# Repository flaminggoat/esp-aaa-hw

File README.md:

# ESP AAA

An AAA battery powered ESP32-C3 board.

# Revisions

* v1.0 - Faulty, Will not start up from an AAA cell, unsuitable boost converter IC used, which requires 1.8V to startup.

# License

Licensed under CERN-OHL-W 
https://cern-ohl.web.cern.ch/

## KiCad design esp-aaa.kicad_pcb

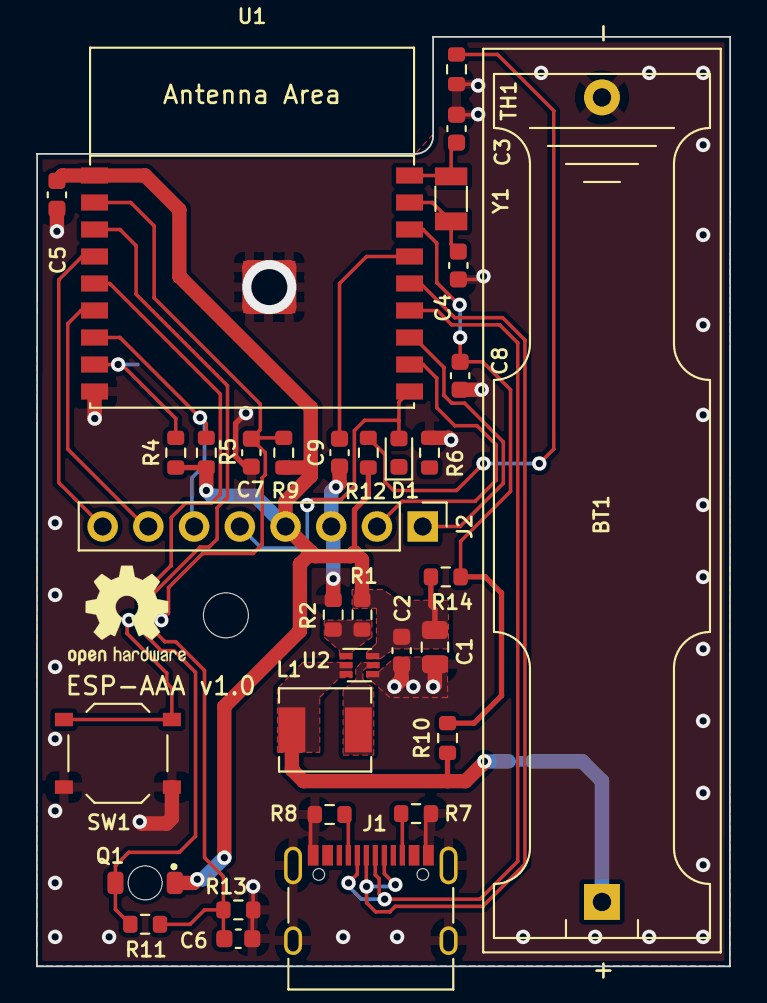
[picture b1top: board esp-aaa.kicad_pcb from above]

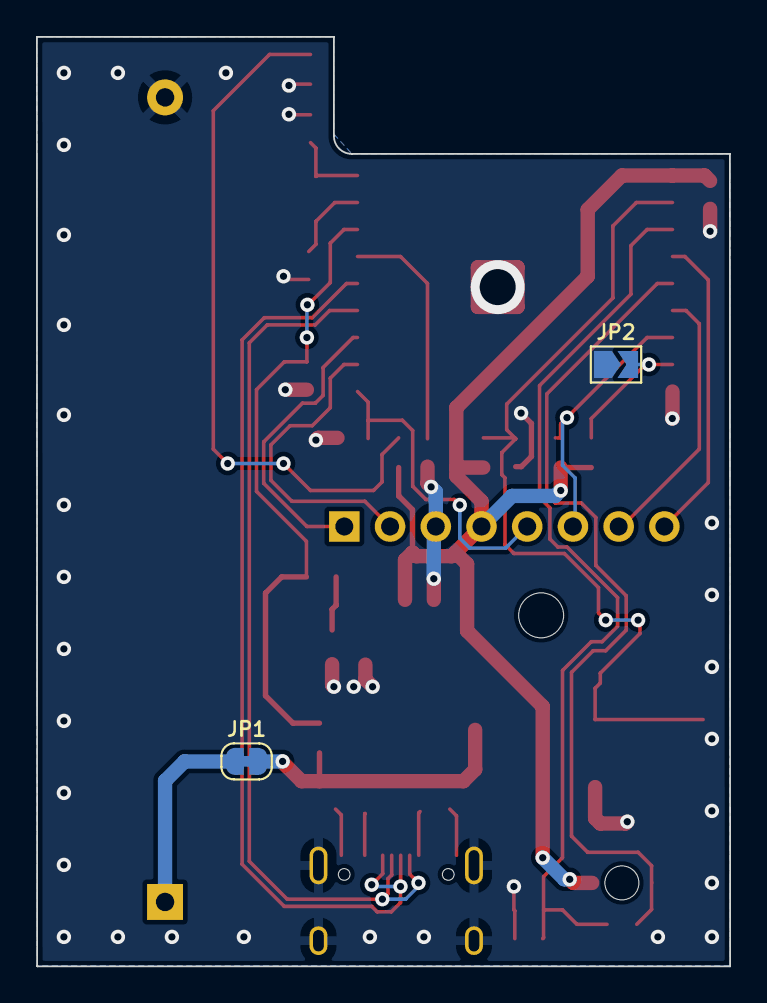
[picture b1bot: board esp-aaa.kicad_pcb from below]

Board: 2 copper layers, 38.5 x 51.6 mm, 36 parts (2 on the bottom side), 25 nets.

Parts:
BT1: AAA; BatteryHolder_Keystone_2466_1xAAA
C1: 22u; C_0805_2012Metric
C2, C5, C7: 1u; C_0603_1608Metric
C3, C4: 18p; C_0603_1608Metric
C6, C8, C9: 0.1u; C_0603_1608Metric
D1: LED; LED_0603_1608Metric
H1: MountingHole; MountingHole_2.5mm
J1: USB_C_Receptacle_USB2.0; USB_C_Receptacle_XKB_U262-16XN-4BVC11
J2: Conn_01x08_Female; PinHeader_1x08_P2.54mm_Vertical
JP1: SolderJumper_2_Bridged; SolderJumper-2_P1.3mm_Bridged_RoundedPad1.0x1.5mm
JP2: SolderJumper_2_Open; SolderJumper-2_P1.3mm_Open_TrianglePad1.0x1.5mm
L1: 1u; L_Chilisin_BMRA00040415
Q1: IN-S126BTNPT; SML-810TB
R1: 300k; R_0603_1608Metric
R2: 1.3M; R_0603_1608Metric
R4, R5, R9, R10, R14: 10k; R_0603_1608Metric
R6: 1.2k; R_0603_1608Metric
R7, R8: 5.1k; R_0603_1608Metric
R11, R12, R13: 100k; R_0603_1608Metric
SW1: SW_Push; SW_Push_1P1T_XKB_TS-1187A
TH1: TX06F103F3435ER; R_0603_1608Metric
U1: ESP32-C3-WROOM-02
U2: TPS61023; SOT-563
Y1: Q13FC1350000400; Crystal_SMD_3215-2Pin_3.2x1.5mm

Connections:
+3V3: C1.1, C2.1, C5.1, J2.4, Q1.1 (C), R2.2, R4.1, R5.1, R9.2, R12.1, R14.1, U1.1 (3V3), U2.6 (VOUT)
/D+: J1.A6 (D+), J1.B6 (D+), U1.14 (GPIO19/USB_D+)
/D-: J1.A7 (D-), J1.B7 (D-), U1.13 (GPIO18/USB_D-)
/G5: J2.8, U1.4 (GPIO5/ADC2_CH0)
/G7: J2.7, U1.6 (GPIO7)
/G8: J2.6, R5.2, U1.7 (GPIO8)
/G9: JP2.2 (B), R4.2, U1.8 (GPIO9)
/G10: D1.2 (A), J2.5, U1.10 (GPIO10)
/PHOTO_INT: Q1.2 (E), R11.1, U1.5 (GPIO6)
/PHOTO_SENS: C6.1, R11.2, R13.1, U1.3 (GPIO4/ADC1_CH4)
/RXD: J2.2, U1.11 (GPIO20/U0RXD)
/TEMP_SENS: C9.1, R12.2, TH1.1, U1.15 (GPIO3/ADC1_CH3)
/TXD: J2.1, U1.12 (GPIO21/U0TXD)
/VBAT_SENS: C8.1, R10.2, R14.2, U1.16 (GPIO2/ADC1_CH2)
GND: BT1.2 (-), C1.2, C2.2, C3.1, C4.1, C5.2, C6.2, C7.2, C8.2, C9.2, J1.A1 (GND), J1.A12 (GND), J1.B1 (GND), J1.B12 (GND), J1.S1 (SHIELD), J2.3, JP2.1 (A), R1.1, R6.1, R7.2, R8.2, R13.2, SW1.2, TH1.2, U1.9 (GND), U1.19 (GND), U2.4 (GND)
unnamed: BT1.1 (+), JP1.1 (A)
unnamed: D1.1 (K), R6.2
unnamed: J1.A5 (CC1), R8.1
unnamed: J1.B5 (CC2), R7.1
unnamed: JP1.2 (B), L1.1, R10.1, U2.2 (EN), U2.3 (VIN)
unnamed: C7.1, R9.1, SW1.1, U1.2 (EN/CHIP_PU)
unnamed: C3.2, U1.18 (GPIO0/ADC1_CH0/XTAL_32K_P), Y1.1
unnamed: C4.2, U1.17 (GPIO1/ADC1_CH1/XTAL_32K_N), Y1.2
unnamed: R1.2, R2.1, U2.1 (FB)
unnamed: L1.2, U2.5 (SW)

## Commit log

2024-03-07 initial
